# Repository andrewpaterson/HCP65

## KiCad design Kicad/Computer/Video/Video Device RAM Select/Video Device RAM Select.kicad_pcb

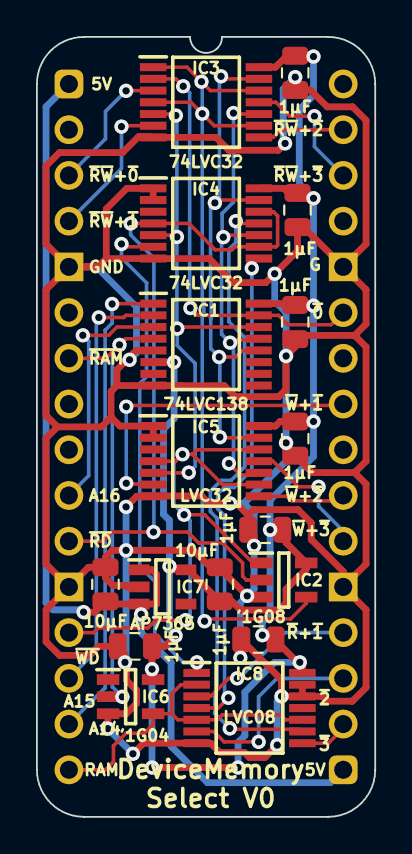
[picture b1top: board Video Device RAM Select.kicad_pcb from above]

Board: 2 copper layers, 18.8 x 43.3 mm, 18 parts (0 on the bottom side), 28 nets.

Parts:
C1, C2, C3, C4, C5, C6, C7: 1μF; C_0805
C8, C9: 10µF; C_0805
IC1: 74LVC138APW-Q100J; SOP65P640X110-16N
IC2: 74LVC1G08GV,125; SOT95P275X110-5N
IC3, IC4, IC5: 74LVC32APW,118; SOP65P640X110-14N
IC6: 74LVC1G04GV,125; SOT95P275X110-5N
IC7: AP7365-33WG-7; SOT95P285X130-5N
IC8: 74LVC08APW,112; SOP65P640X110-14N
J1: Board 2x16 W15.24mm; DIP-32_Board_W15.24mm

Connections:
5V: C8.1, IC7.1 (6VIn), IC7.3 (EN), J1.1, J1.17
(~RD·~WD)+~Device RAM 0: IC3.3 (1Y), J1.3
(~RD·~WD)+~Device RAM 1: IC3.6 (2Y), J1.4
(~RD·~WD)+~Device RAM 2: IC3.8 (3Y), J1.31
(~RD·~WD)+~Device RAM 3: IC3.11 (4Y), J1.30
/3.3V: C1.1, C2.1, C3.1, C4.1, C5.1, C6.1, C7.1, C9.1, IC1.6 (E3), IC1.16 (3V), IC2.5 (3V), IC3.14 (3V), IC4.14 (3V), IC5.14 (3V), IC6.5 (3V), IC7.5 (3.3VOut), IC8.14 (3V)
/~Device RAM 1: IC1.14 (~Y1), IC3.5 (2B), IC4.5 (2B), IC5.5 (2B)
/~Device RAM 2: IC1.13 (~Y2), IC3.10 (3B), IC4.10 (3B), IC5.10 (3B)
/~Device RAM 3: IC1.12 (~Y3), IC3.13 (4B), IC4.13 (4B), IC5.13 (4B)
/~RD+~Device RAM 1: IC4.6 (2Y), IC8.1 (1A)
/~RD+~Device RAM 2: IC4.8 (3Y), IC8.4 (2A)
/~RD+~Device RAM 3: IC4.11 (4Y), IC8.9 (3A)
/~RD·~WD: IC2.4 (Y), IC3.1 (1A), IC3.4 (2A), IC3.9 (3A), IC3.12 (4A)
A14: IC1.1 (A0), J1.15
A15: IC1.2 (A1), J1.14
A16: IC1.3 (A2), J1.10
Device RAM: IC6.4 (Y), IC8.2 (1B), IC8.5 (2B), IC8.10 (3B), J1.16
GND: C1.2, C2.2, C3.2, C4.2, C5.2, C6.2, C7.2, C8.2, C9.2, IC1.5 (~E2), IC1.8 (GND), IC2.3 (GND), IC3.7 (GND), IC4.1 (1A), IC4.2 (1B), IC4.7 (GND), IC5.1 (1A), IC5.2 (1B), IC5.7 (GND), IC6.3 (GND), IC7.2 (GND), IC8.7 (GND), IC8.12 (4A), IC8.13 (4B), J1.5, J1.12, J1.21, J1.28
~Device RAM 0: IC1.15 (~Y0), IC3.2 (1B), J1.27
~Device RAM: IC1.4 (~E1), IC6.2 (A), J1.7
~RD: IC2.2 (A), IC4.4 (2A), IC4.9 (3A), IC4.12 (4A), J1.11
~Read Device RAM 1: IC8.3 (1Y), J1.20
~Read Device RAM 2: IC8.6 (2Y), J1.19
~Read Device RAM 3: IC8.8 (3Y), J1.18
~WD: IC2.1 (B), IC5.4 (2A), IC5.9 (3A), IC5.12 (4A), J1.13
~WD+~Device RAM 1: IC5.6 (2Y), J1.25
~WD+~Device RAM 2: IC5.8 (3Y), J1.23
~WD+~Device RAM 3: IC5.11 (4Y), J1.22

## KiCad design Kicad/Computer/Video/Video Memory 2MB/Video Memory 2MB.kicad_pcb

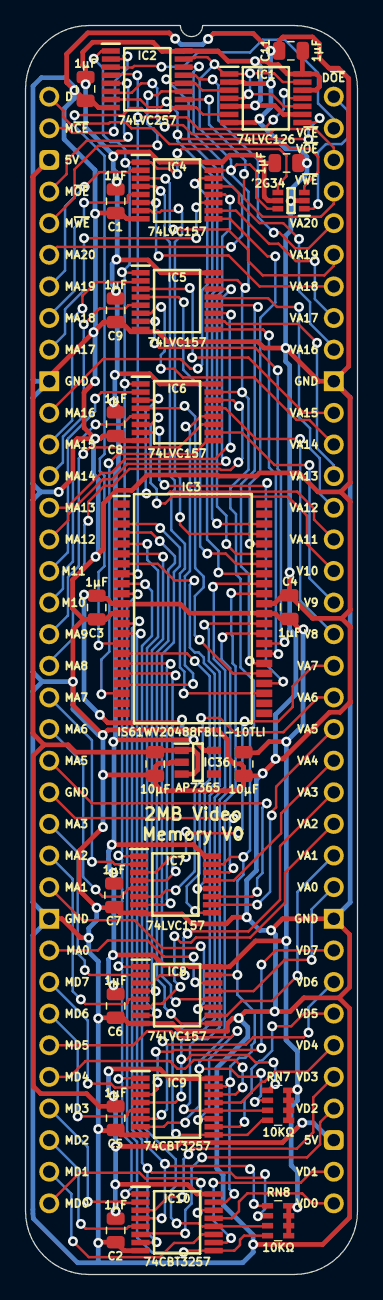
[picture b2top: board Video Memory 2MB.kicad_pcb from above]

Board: 2 copper layers, 26.7 x 100.3 mm, 29 parts (0 on the bottom side), 103 nets.

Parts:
C1, C2, C3, C4, C5, C6, C7, C8, C9, C10, C11, C12: 1μF; C_0805
C41, C42: 10μF; C_0805
IC1: 74LVC126APW-Q100J; SOP65P640X110-14N
IC2: 74LVC257APW,118; SOP65P640X110-16N
IC3: IS61WV20488FBLL-10TLI; SOP80P1176X120-44N
IC4, IC5, IC6, IC7, IC8: 74LVC157APW,118; SOP65P640X110-16N
IC9, IC10: SN74CBT3257CPWR; SOP65P640X120-16N
IC11: 74LVC2G34GW,125; 74LVC2G34GW125
IC36: AP7365-33WG-7; SOT95P285X130-5N
J3: Board 2x36 W22.86mm; DIP-72_Board_W22.86mm
RN7, RN8: CAY16-103J4LF; CAY16-J4

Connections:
5V: C2.1, C5.1, C41.1, IC9.16 (5V), IC10.16 (5V), IC36.1 (6VIn), IC36.3 (EN), J3.3, J3.39
/3.3V: C1.1, C3.1, C4.1, C6.1, C7.1, C8.1, C9.1, C10.1, C11.1, C12.1, C42.1, IC1.5 (2A), IC1.9 (3A), IC1.12 (4A), IC1.14 (3V), IC2.16 (3V), IC3.11 (3V), IC3.33 (3V), IC4.16 (3V), IC5.16 (3V), IC6.16 (3V), IC7.16 (3V), IC8.16 (3V), IC11.5 (3V), IC36.5 (3.3VOut), RN7.5 (R4), RN7.6 (R3), RN7.7 (R2), RN7.8 (R1), RN8.5 (R4), RN8.6 (R3), RN8.7 (R2), RN8.8 (R1)
/D: IC2.1 (S), IC4.1 (S), IC5.1 (S), IC6.1 (S), IC7.1 (S), IC8.1 (S), IC9.1 (S), IC10.1 (S), IC11.4 (2Y)
/D~OE: IC1.1 (1OE), IC1.4 (2OE), IC1.10 (3OE), IC1.13 (4OE), IC2.15 (~OE), IC4.15 (~E), IC5.15 (~E), IC6.15 (~E), IC7.15 (~E), IC8.15 (~E), IC9.15 (~OE), IC10.15 (~OE), IC11.6 (1Y)
/SA0: IC3.3 (A0), IC8.12 (4Y)
/SA1: IC3.4 (A1), IC8.9 (3Y)
/SA2: IC3.5 (A2), IC8.7 (2Y)
/SA3: IC3.6 (A3), IC8.4 (1Y)
/SA4: IC3.7 (A4), IC7.12 (4Y)
/SA5: IC3.16 (A5), IC7.9 (3Y)
/SA6: IC3.17 (A6), IC7.7 (2Y)
/SA7: IC3.18 (A7), IC7.4 (1Y)
/SA8: IC3.19 (A8), IC6.12 (4Y)
/SA9: IC3.20 (A9), IC6.9 (3Y)
/SA10: IC3.26 (A10), IC6.7 (2Y)
/SA11: IC3.27 (A11), IC6.4 (1Y)
/SA12: IC3.28 (A12), IC5.12 (4Y)
/SA13: IC3.29 (A13), IC5.9 (3Y)
/SA14: IC3.30 (A14), IC5.7 (2Y)
/SA15: IC3.38 (A15), IC5.4 (1Y)
/SA16: IC3.39 (A16), IC4.12 (4Y)
/SA17: IC3.40 (A17), IC4.9 (3Y)
/SA18: IC3.41 (A18), IC4.7 (2Y)
/SA19: IC3.25 (A19), IC4.4 (1Y)
/SA20: IC1.3 (1Y), IC2.12 (4Y), IC3.42 (A20)
/SD0: IC3.9 (D0), IC10.12 (4A), RN8.3 (R3)
/SD1: IC3.10 (D1), IC10.9 (3A), RN8.4 (R4)
/SD2: IC3.13 (D2), IC10.7 (2A), RN8.2 (R2)
/SD3: IC3.14 (D3), IC10.4 (1A), RN8.1 (R1)
/SD4: IC3.31 (D4), IC9.12 (4A), RN7.3 (R3)
/SD5: IC3.32 (D5), IC9.9 (3A), RN7.4 (R4)
/SD6: IC3.35 (D6), IC9.7 (2A), RN7.2 (R2)
/SD7: IC3.36 (D7), IC9.4 (1A), RN7.1 (R1)
/S~CE: IC1.11 (4Y), IC2.4 (1Y), IC3.8 (~CE)
/S~OE: IC1.8 (3Y), IC2.7 (2Y), IC3.37 (~OE)
/S~WE: IC1.6 (2Y), IC2.9 (3Y), IC3.15 (~WE)
D_{I}: IC11.3 (2A), J3.1
D~OE_{I}: IC11.1 (1A), J3.72
GND: C1.2, C2.2, C3.2, C4.2, C5.2, C6.2, C7.2, C8.2, C9.2, C10.2, C11.2, C12.2, C41.2, C42.2, IC1.2 (1A), IC1.7 (GND), IC2.8 (GND), IC3.12 (GND), IC3.34 (GND), IC4.8 (GND), IC5.8 (GND), IC6.8 (GND), IC7.8 (GND), IC8.8 (GND), IC9.8 (GND), IC10.8 (GND), IC11.2 (GND), IC36.2 (GND), J3.10, J3.27, J3.46, J3.63
MA0: IC8.14 (4I0), J3.28
MA1: IC8.11 (3I0), J3.26
MA2: IC8.5 (2I0), J3.25
MA3: IC8.2 (1I0), J3.24
MA4: IC7.14 (4I0), J3.23
MA5: IC7.11 (3I0), J3.22
MA6: IC7.5 (2I0), J3.21
MA7: IC7.2 (1I0), J3.20
MA8: IC6.14 (4I0), J3.19
MA9: IC6.11 (3I0), J3.18
MA10: IC6.5 (2I0), J3.17
MA11: IC6.2 (1I0), J3.16
MA12: IC5.14 (4I0), J3.15
MA13: IC5.11 (3I0), J3.14
MA14: IC5.5 (2I0), J3.13
MA15: IC5.2 (1I0), J3.12
MA16: IC4.14 (4I0), J3.11
MA17: IC4.11 (3I0), J3.9
MA18: IC4.5 (2I0), J3.8
MA19: IC4.2 (1I0), J3.7
MA20: IC2.14 (4I0), J3.6
MD0: IC10.14 (4B1), J3.36
MD1: IC10.11 (3B1), J3.35
MD2: IC10.5 (2B1), J3.34
MD3: IC10.2 (1B1), J3.33
MD4: IC9.14 (4B1), J3.32
MD5: IC9.11 (3B1), J3.31
MD6: IC9.5 (2B1), J3.30
MD7: IC9.2 (1B1), J3.29
M~CE: IC2.2 (1I0), J3.2
M~OE: IC2.5 (2I0), J3.4
M~WE: IC2.11 (3I0), J3.5
VA0: IC8.13 (4I1), J3.47
VA1: IC8.10 (3I1), J3.48
VA2: IC8.6 (2I1), J3.49
VA3: IC8.3 (1I1), J3.50
VA4: IC7.13 (4I1), J3.51
VA5: IC7.10 (3I1), J3.52
VA6: IC7.6 (2I1), J3.53
VA7: IC7.3 (1I1), J3.54
VA8: IC6.13 (4I1), J3.55
VA9: IC6.10 (3I1), J3.56
VA10: IC6.6 (2I1), J3.57
VA11: IC6.3 (1I1), J3.58
VA12: IC5.13 (4I1), J3.59
VA13: IC5.10 (3I1), J3.60
VA14: IC5.6 (2I1), J3.61
VA15: IC5.3 (1I1), J3.62
VA16: IC4.13 (4I1), J3.64
VA17: IC4.10 (3I1), J3.65
VA18: IC4.6 (2I1), J3.66
VA19: IC4.3 (1I1), J3.67
VA20: IC2.13 (4I1), J3.68
VD0: IC10.13 (4B2), J3.37
VD1: IC10.10 (3B2), J3.38
VD2: IC10.6 (2B2), J3.40
VD3: IC10.3 (1B2), J3.41
VD4: IC9.13 (4B2), J3.42
VD5: IC9.10 (3B2), J3.43
VD6: IC9.6 (2B2), J3.44
VD7: IC9.3 (1B2), J3.45
V~CE: IC2.3 (1I1), J3.71
V~OE: IC2.6 (2I1), J3.70
V~WE: IC2.10 (3I1), J3.69

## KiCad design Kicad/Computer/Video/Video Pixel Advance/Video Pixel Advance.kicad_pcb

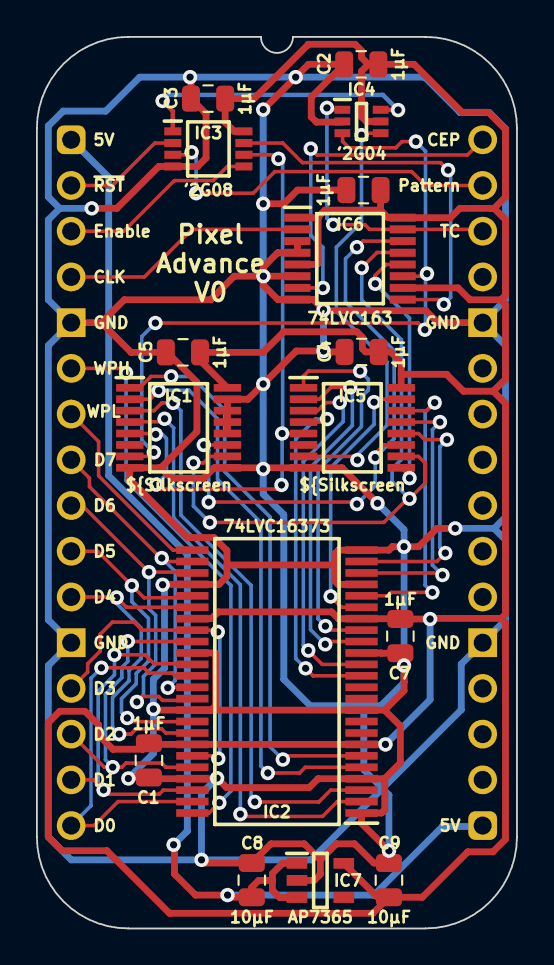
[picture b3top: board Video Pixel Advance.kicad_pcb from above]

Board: 2 copper layers, 26.7 x 49.5 mm, 17 parts (0 on the bottom side), 39 nets.

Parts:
C1, C2, C3, C4, C5, C6, C7: 1μF; C_0805
C8, C9: 10µF; C_0805
IC1, IC5: PI3B3251QE; SOP64P599X175-16N
IC2: 74LVC16373ADL,118; SOP64P1025X280-48N
IC3: 74LVC2G08DP-Q100H; SOP65P400X110-8N
IC4: 74LVC2G04GW-Q100H; SOP65P210X110-6N
IC6: 74LVC163PW,118; SOP65P640X110-16N
IC7: AP7365-33WG-7; SOT95P285X130-5N
J1: Board 2x16 W22.86mm; DIP-32_Board_W22.86mm

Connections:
5V: C8.1, IC7.1 (6VIn), IC7.3 (EN), J1.1, J1.17
/3.3V: C1.1, C2.1, C3.1, C4.1, C5.1, C6.1, C7.1, C9.1, IC1.16 (3V), IC2.7 (3V), IC2.18 (3V), IC2.31 (3V), IC2.42 (3V), IC3.8 (3V), IC4.5 (3V), IC5.16 (3V), IC6.1 (~MR), IC6.5 (D2), IC6.10 (CET), IC6.16 (3V), IC7.5 (3.3VOut)
/Q0: IC1.11 (S0), IC5.11 (S0), IC6.14 (Q0)
/Q1: IC1.10 (S1), IC5.10 (S1), IC6.13 (Q1)
/Q2: IC5.9 (S2), IC6.12 (Q2)
/Q3: IC1.7 (~OE), IC4.3 (2A), IC6.11 (Q3)
/RPS0: IC2.23 (2Q7), IC5.12 (I7)
/RPS1: IC2.22 (2Q6), IC5.13 (I6)
/RPS2: IC2.20 (2Q5), IC5.14 (I5)
/RPS3: IC2.19 (2Q4), IC5.15 (I4)
/RPS4: IC2.17 (2Q3), IC5.1 (I3)
/RPS5: IC2.16 (2Q2), IC5.2 (I2)
/RPS6: IC2.14 (2Q1), IC5.3 (I1)
/RPS7: IC2.13 (2Q0), IC5.4 (I0)
/RPS8: IC1.1 (I3), IC2.6 (1Q3)
/RPS9: IC1.2 (I2), IC2.5 (1Q2)
/RPS10: IC1.3 (I1), IC2.3 (1Q1)
/RPS11: IC1.4 (I0), IC2.2 (1Q0)
/Y: IC1.5 (Y), IC3.6 (2B), IC5.5 (Y)
/~PE: IC3.7 (1Y), IC6.9 (~PE)
/~Q3: IC4.4 (2Y), IC5.7 (~OE)
/~TC: IC3.1 (1A), IC4.6 (1Y)
CEP: IC6.7 (CEP), J1.32
CLK: IC6.2 (CP), J1.4
D0: IC2.36 (2D0), IC2.47 (1D0), J1.16
D1: IC2.35 (2D1), IC2.46 (1D1), J1.15
D2: IC2.33 (2D2), IC2.44 (1D2), J1.14
D3: IC2.32 (2D3), IC2.43 (1D3), J1.13
D4: IC2.30 (2D4), IC2.41 (1D4), J1.11
D5: IC2.29 (2D5), IC2.40 (1D5), J1.10
D6: IC2.27 (2D6), IC2.38 (1D6), J1.9
D7: IC2.26 (2D7), IC2.37 (1D7), J1.8
Enable Pattern: IC3.5 (2A), J1.3
GND: C1.2, C2.2, C3.2, C4.2, C5.2, C6.2, C7.2, C8.2, C9.2, IC1.8 (GND), IC1.9 (S2), IC1.12 (I7), IC1.13 (I6), IC1.14 (I5), IC1.15 (I4), IC2.1 (1~OE), IC2.4 (GND), IC2.10 (GND), IC2.15 (GND), IC2.21 (GND), IC2.24 (2~OE), IC2.28 (GND), IC2.34 (GND), IC2.39 (GND), IC2.45 (GND), IC3.4 (GND), IC4.2 (GND), IC5.8 (GND), IC6.3 (D0), IC6.4 (D1), IC6.6 (D3), IC6.8 (GND), IC7.2 (GND), J1.5, J1.12, J1.21, J1.28
Selected Pattern: IC3.3 (2Y), J1.31
TC: IC4.1 (1A), IC6.15 (TC), J1.30
Write Pattern High: IC2.25 (2LE), J1.7
Write Pattern Low: IC2.48 (1LE), J1.6
~Reset: IC3.2 (1B), J1.2

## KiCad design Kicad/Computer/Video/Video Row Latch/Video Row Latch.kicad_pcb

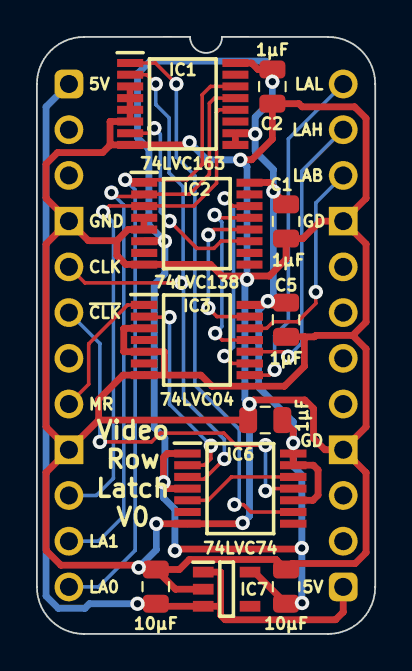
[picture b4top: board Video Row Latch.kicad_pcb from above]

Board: 2 copper layers, 18.8 x 33.2 mm, 12 parts (0 on the bottom side), 19 nets.

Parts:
C1, C2, C4, C5: 1μF; C_0805
C8, C9: 10μF; C_0805
IC1: 74LVC163PW,118; SOP65P640X110-16N
IC2: 74LVC138APW-Q100J; SOP65P640X110-16N
IC3: 74LVC04APW,118; SOP65P640X110-14N
IC6: 74LVC74APW,118; SOP65P640X110-14N
IC7: AP7365-33WG-7; SOT95P285X130-5N
J1: Board 2x12 W15.24mm; DIP-24_Board_W15.24mm

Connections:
5V: C8.1, IC7.1 (6VIn), IC7.3 (EN), J1.1, J1.13
/3.3V: C1.1, C2.1, C4.1, C5.1, C9.1, IC1.9 (~PE), IC1.10 (CET), IC1.16 (3V), IC2.6 (E3), IC2.16 (3V), IC3.14 (3V), IC6.1 (~1RD), IC6.4 (~1SD), IC6.10 (~2SD), IC6.13 (~2RD), IC6.14 (3V), IC7.5 (3.3VOut)
/CEP: IC1.7 (CEP), IC2.11 (~Y4)
/~Load Address Bank: IC2.12 (~Y3), IC3.13 (6A)
/~Load Address High: IC2.13 (~Y2), IC3.11 (5A)
/~Load Address Low: IC2.14 (~Y1), IC3.9 (4A)
/~MR: IC3.2 (1Y), IC6.2 (1D)
/~MR1: IC6.5 (1Q), IC6.12 (2D)
/~MR2: IC1.1 (~MR), IC6.9 (2Q)
CLK: IC1.2 (CP), IC6.3 (1CP), J1.5
GND: C1.2, C2.2, C4.2, C5.2, C8.2, C9.2, IC1.3 (D0), IC1.4 (D1), IC1.5 (D2), IC1.6 (D3), IC1.8 (GND), IC2.4 (~E1), IC2.5 (~E2), IC2.8 (GND), IC3.3 (2A), IC3.5 (3A), IC3.7 (GND), IC6.7 (GND), IC7.2 (GND), J1.4, J1.9, J1.16, J1.21
LA0: IC1.14 (Q0), IC2.1 (A0), J1.12
LA1: IC1.13 (Q1), IC2.2 (A1), J1.11
LA2: IC1.12 (Q2), IC2.3 (A2), J1.10
Load Address Bank: IC3.12 (6Y), J1.22
Load Address High: IC3.10 (5Y), J1.23
Load Address Low: IC3.8 (4Y), J1.24
MR: IC3.1 (1A), J1.8
~CLK: IC6.11 (2CP), J1.6

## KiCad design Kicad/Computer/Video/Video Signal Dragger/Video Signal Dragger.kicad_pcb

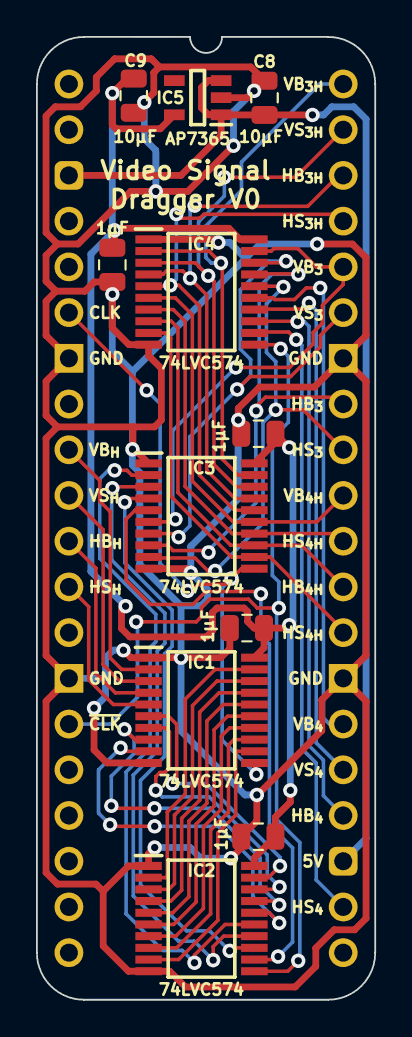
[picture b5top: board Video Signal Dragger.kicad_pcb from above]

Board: 2 copper layers, 18.8 x 53.5 mm, 12 parts (0 on the bottom side), 41 nets.

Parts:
C1, C2, C3, C4: 1μF; C_0805
C8, C9: 10µF; C_0805
IC1, IC2, IC3, IC4: 74LVC574APW,118; SOP65P640X110-20N
IC5: AP7365-33WG-7; SOT95P285X130-5N
J2: Board 2x20 W15.24mm; DIP-40_Board_W15.24mm

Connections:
5V: C8.1, IC5.1 (6VIn), IC5.3 (EN), J2.3, J2.23
/3.3V: C1.1, C2.1, C3.1, C4.1, C9.1, IC1.20 (3V), IC2.20 (3V), IC3.20 (3V), IC4.20 (3V), IC5.5 (3.3VOut)
/Horizontal Blank _{CYCLE 1H}: IC1.17 (Q2), IC2.4 (D2)
/Horizontal Blank _{CYCLE 1}: IC1.8 (D6), IC2.17 (Q2)
/Horizontal Blank _{CYCLE 2H}: IC1.13 (Q6), IC2.8 (D6)
/Horizontal Blank _{CYCLE 2}: IC2.13 (Q6), IC3.4 (D2)
/Horizontal Sync _{CYCLE 1H}: IC1.16 (Q3), IC2.5 (D3)
/Horizontal Sync _{CYCLE 1}: IC1.9 (D7), IC2.16 (Q3)
/Horizontal Sync _{CYCLE 2H}: IC1.12 (Q7), IC2.9 (D7)
/Horizontal Sync _{CYCLE 2}: IC2.12 (Q7), IC3.5 (D3)
/Vertical Blank _{CYCLE 1H}: IC1.19 (Q0), IC2.2 (D0)
/Vertical Blank _{CYCLE 1}: IC1.6 (D4), IC2.19 (Q0)
/Vertical Blank _{CYCLE 2H}: IC1.15 (Q4), IC2.6 (D4)
/Vertical Blank _{CYCLE 2}: IC2.15 (Q4), IC3.2 (D0)
/Vertical Sync _{CYCLE 1H}: IC1.18 (Q1), IC2.3 (D1)
/Vertical Sync _{CYCLE 1}: IC1.7 (D5), IC2.18 (Q1)
/Vertical Sync _{CYCLE 2H}: IC1.14 (Q5), IC2.7 (D5)
/Vertical Sync _{CYCLE 2}: IC2.14 (Q5), IC3.3 (D1)
GND: C1.2, C2.2, C3.2, C4.2, C8.2, C9.2, IC1.1 (~OE), IC1.10 (GND), IC2.1 (~OE), IC2.10 (GND), IC3.1 (~OE), IC3.10 (GND), IC4.1 (~OE), IC4.10 (GND), IC5.2 (GND), J2.7, J2.14, J2.27, J2.34
Horizontal Blank _{CYCLE 3H}: IC3.17 (Q2), IC4.4 (D2), J2.38
Horizontal Blank _{CYCLE 3}: IC3.8 (D6), IC4.17 (Q2), J2.33
Horizontal Blank _{CYCLE 4H}: IC3.13 (Q6), IC4.8 (D6), J2.29
Horizontal Blank _{CYCLE 4}: IC4.13 (Q6), J2.24
Horizontal Blank _{HALF CYCLE}: IC1.4 (D2), J2.11
Horizontal Sync _{CYCLE 3H}: IC3.16 (Q3), IC4.5 (D3), J2.37
Horizontal Sync _{CYCLE 3}: IC3.9 (D7), IC4.16 (Q3), J2.32
Horizontal Sync _{CYCLE 4H}: IC3.12 (Q7), IC4.9 (D7), J2.28
Horizontal Sync _{CYCLE 4}: IC4.12 (Q7), J2.22
Horizontal Sync _{HALF CYCLE}: IC1.5 (D3), J2.12
Pixel CLK: IC1.11 (CP), IC3.11 (CP), J2.6
Vertical Blank _{CYCLE 3H}: IC3.19 (Q0), IC4.2 (D0), J2.40
Vertical Blank _{CYCLE 3}: IC3.6 (D4), IC4.19 (Q0), J2.36
Vertical Blank _{CYCLE 4H}: IC3.15 (Q4), IC4.6 (D4), J2.31
Vertical Blank _{CYCLE 4}: IC4.15 (Q4), J2.26
Vertical Blank _{HALF CYCLE}: IC1.2 (D0), J2.9
Vertical Sync _{CYCLE 3H}: IC3.18 (Q1), IC4.3 (D1), J2.39
Vertical Sync _{CYCLE 3}: IC3.7 (D5), IC4.18 (Q1), J2.35
Vertical Sync _{CYCLE 4H}: IC3.14 (Q5), IC4.7 (D5), J2.30
Vertical Sync _{CYCLE 4}: IC4.14 (Q5), J2.25
Vertical Sync _{HALF CYCLE}: IC1.3 (D1), J2.10
~Pixel CLK: IC2.11 (CP), IC4.11 (CP), J2.15

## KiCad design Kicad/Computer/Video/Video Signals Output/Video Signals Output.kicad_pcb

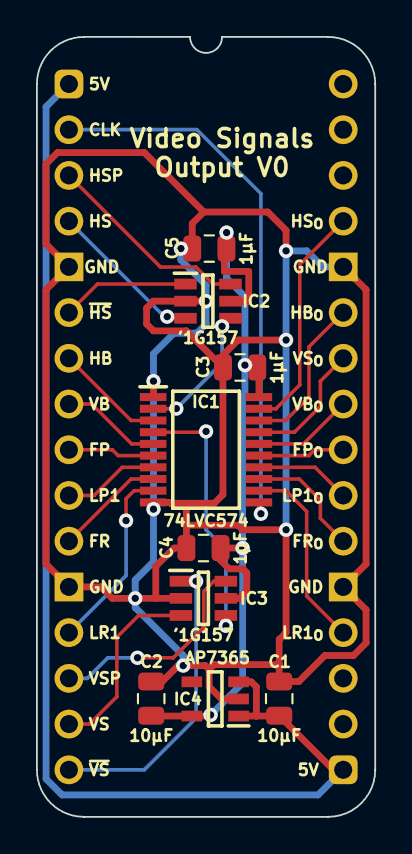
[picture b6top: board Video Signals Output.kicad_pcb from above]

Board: 2 copper layers, 18.8 x 43.3 mm, 10 parts (0 on the bottom side), 26 nets.

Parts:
C1, C2: 10µF; C_0805
C3, C4, C5: 1μF; C_0805
IC1: 74LVC574APW,118; SOP65P640X110-20N
IC2, IC3: 74LVC1G157GV,125; 74LVC1G157GV125
IC4: AP7365-33WG-7; SOT95P285X130-5N
J1: Board 2x16 W15.24mm; DIP-32_Board_W15.24mm

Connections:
5V: C1.1, IC4.1 (6VIn), IC4.3 (EN), J1.1, J1.17
/3.3V: C2.1, C3.1, C4.1, C5.1, IC1.20 (3V), IC2.5 (3V), IC3.5 (3V), IC4.5 (3.3VOut)
/Horizontal Sync _{SEL}: IC1.2 (D0), IC2.4 (Y)
/Vertical Sync _{SEL}: IC1.4 (D2), IC3.4 (Y)
CLK: IC1.11 (CP), J1.2
First Pixel: IC1.6 (D4), J1.9
First Pixel _{HALF CYCLE}: IC1.15 (Q4), J1.24
First Row: IC1.8 (D6), J1.11
First Row _{HALF CYCLE}: IC1.13 (Q6), J1.22
GND: C1.2, C2.2, C3.2, C4.2, C5.2, IC1.1 (~OE), IC1.10 (GND), IC2.2 (GND), IC3.2 (GND), IC4.2 (GND), J1.5, J1.12, J1.21, J1.28
Horizontal Blank: IC1.3 (D1), J1.7
Horizontal Blank _{HALF CYCLE}: IC1.18 (Q1), J1.27
Horizontal Sync: IC2.3 (I0), J1.4
Horizontal Sync Polarity: IC2.6 (S), J1.3
Horizontal Sync _{HALF CYCLE}: IC1.19 (Q0), J1.29
Last Pixel + 1: IC1.7 (D5), J1.10
Last Pixel + 1 _{HALF CYCLE}: IC1.14 (Q5), J1.23
Last Row + 1: IC1.9 (D7), J1.13
Last Row + 1 _{HALF CYCLE}: IC1.12 (Q7), J1.20
Vertical Blank: IC1.5 (D3), J1.8
Vertical Blank _{HALF CYCLE}: IC1.16 (Q3), J1.25
Vertical Sync: IC3.3 (I0), J1.15
Vertical Sync Polarity: IC3.6 (S), J1.14
Vertical Sync _{HALF CYCLE}: IC1.17 (Q2), J1.26
~Horizontal Sync: IC2.1 (I1), J1.6
~Vertical Sync: IC3.1 (I1), J1.16

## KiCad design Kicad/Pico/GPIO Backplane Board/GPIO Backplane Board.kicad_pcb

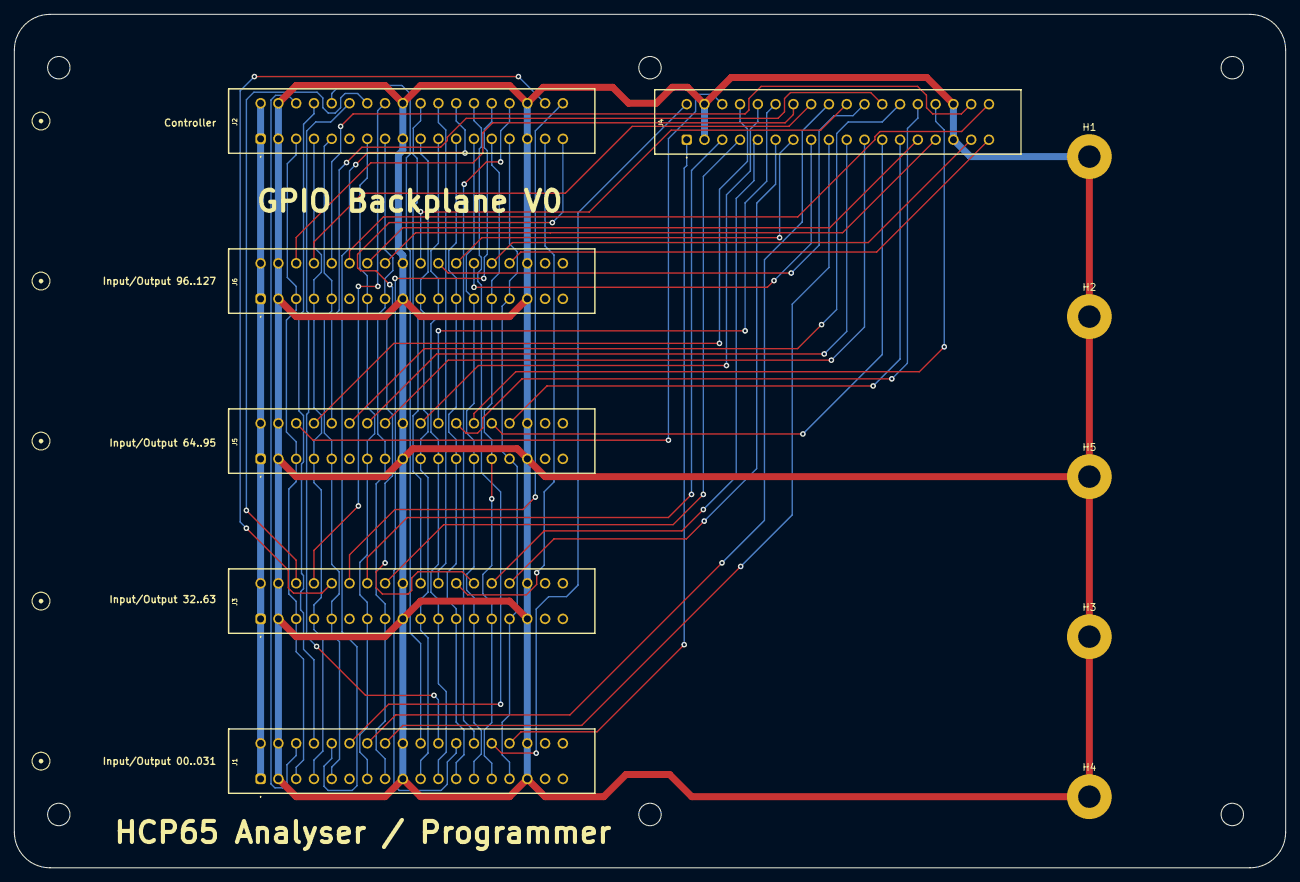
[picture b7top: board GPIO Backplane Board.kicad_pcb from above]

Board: 2 copper layers, 181.6 x 121.9 mm, 22 parts (0 on the bottom side), 61 nets.

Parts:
B1, B2, B3, B4: HCP65_GPIO_32bit_Board
B5: HCP65_GPIO_Controller_Board
H1, H2, H3, H4, H5: MountingHole_Pad; MountingHole_3.2mm_M3_Pad
H6, H7, H8, H9, H10, H11: MountingHole; MountingHole_3.2mm_M3
J1, J2, J3, J4, J5, J6: 2-5530843-7; 255308437

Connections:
/12V: J1.1, J1.2, J2.1, J2.2, J3.1, J3.2, J5.1, J5.2, J6.1, J6.2
/D0: J1.13, J2.13, J3.13, J5.13, J6.13
/D1: J1.15, J2.15, J3.15, J5.15, J6.15
/D2: J1.19, J2.19, J3.19, J5.19, J6.19
/D3: J1.21, J2.21, J3.21, J5.21, J6.21
/D4: J1.23, J2.23, J3.23, J5.23, J6.23
/D5: J1.25, J2.25, J3.25, J5.25, J6.25
/D6: J1.27, J2.27, J3.27, J5.27, J6.27
/D7: J1.29, J2.29, J3.29, J5.29, J6.29
/GND: H1.1, H2.1, H3.1, H4.1, H5.1, J1.3, J1.4, J1.17, J1.18, J1.31, J1.32, J2.3, J2.4, J2.17, J2.18, J2.31, J2.32, J3.3, J3.4, J3.17, J3.18, J3.31, J3.32, J4.3, J4.4, J4.31, J4.32, J5.3, J5.4, J5.17, J5.18, J5.31, J5.32, J6.3, J6.4, J6.17, J6.18, J6.31, J6.32
/Read GD B0 _{0..7}: J1.6, J2.6
/Read GD B0 _{8..15}: J1.8, J2.8
/Read GD B0 _{16..23}: J1.20, J2.10
/Read GD B0 _{24..31}: J1.22, J2.12
/Read GD B0 _{32..39}: J2.14, J3.6
/Read GD B0 _{40..47}: J2.16, J3.8
/Read GD B0 _{48..55}: J2.20, J3.20
/Read GD B0 _{56..63}: J2.22, J3.22
/Read GD B1 _{0..7}: J4.6, J5.6
/Read GD B1 _{8..15}: J4.8, J5.8
/Read GD B1 _{16..23}: J4.10, J5.20
/Read GD B1 _{24..31}: J4.12, J5.22
/Read GD B1 _{32..39}: J4.14, J6.6
/Read GD B1 _{40..47}: J4.16, J6.8
/Read GD B1 _{48..55}: J4.20, J6.20
/Read GD B1 _{56..63}: J4.22, J6.22
/Read GPIO _{ALL}: J1.7, J2.7, J3.7, J5.7, J6.7
/Write Enable: J1.5, J2.5, J3.5, J5.5, J6.5
/Write GD B0 _{0..7}: J1.10, J2.24
/Write GD B0 _{8..15}: J1.12, J2.26
/Write GD B0 _{16..23}: J1.24, J2.28
/Write GD B0 _{24..31}: J1.26, J2.30
/Write GD B0 _{32..39}: J2.34, J3.10
/Write GD B0 _{40..47}: J2.36, J3.12
/Write GD B0 _{48..55}: J2.33, J3.24
/Write GD B0 _{56..63}: J2.35, J3.26
/Write GD B1 _{0..7}: J4.24, J5.10
/Write GD B1 _{8..15}: J4.26, J5.12
/Write GD B1 _{16..23}: J4.28, J5.24
/Write GD B1 _{24..31}: J4.30, J5.26
/Write GD B1 _{32..39}: J4.34, J6.10
/Write GD B1 _{40..47}: J4.36, J6.12
/Write GD B1 _{48..55}: J4.13, J6.24
/Write GD B1 _{56..63}: J4.15, J6.26
/Write GPIO _{ALL}: J1.9, J2.9, J3.9, J5.9, J6.9
/Write OE B0 _{0..7}: J1.14, J4.18
/Write OE B0 _{8..15}: J1.16, J4.17
/Write OE B0 _{16..23}: J1.28, J4.2
/Write OE B0 _{24..31}: J1.30, J4.1
/Write OE B0 _{32..39}: J3.14, J4.5
/Write OE B0 _{40..47}: J3.16, J4.7
/Write OE B0 _{48..55}: J3.28, J4.9
/Write OE B0 _{56..63}: J3.30, J4.11
/Write OE B1 _{0..7}: J4.19, J5.14
/Write OE B1 _{8..15}: J4.21, J5.16
/Write OE B1 _{16..23}: J4.23, J5.28
/Write OE B1 _{24..31}: J4.25, J5.30
/Write OE B1 _{32..39}: J4.27, J6.14
/Write OE B1 _{40..47}: J4.29, J6.16
/Write OE B1 _{48..55}: J4.33, J6.28
/Write OE B1 _{56..63}: J4.35, J6.30

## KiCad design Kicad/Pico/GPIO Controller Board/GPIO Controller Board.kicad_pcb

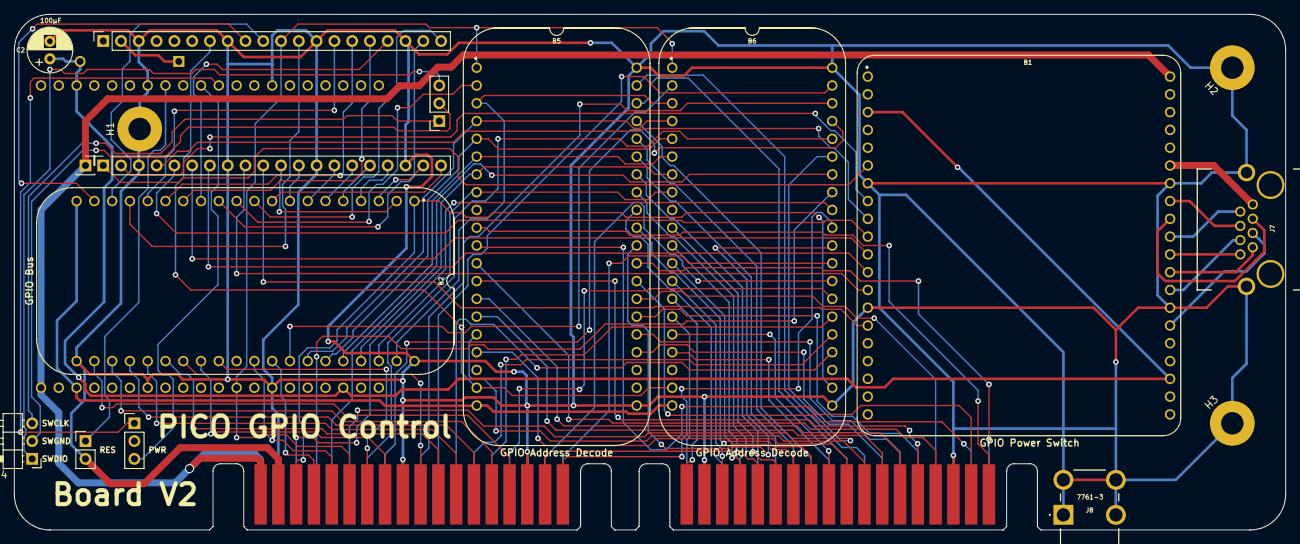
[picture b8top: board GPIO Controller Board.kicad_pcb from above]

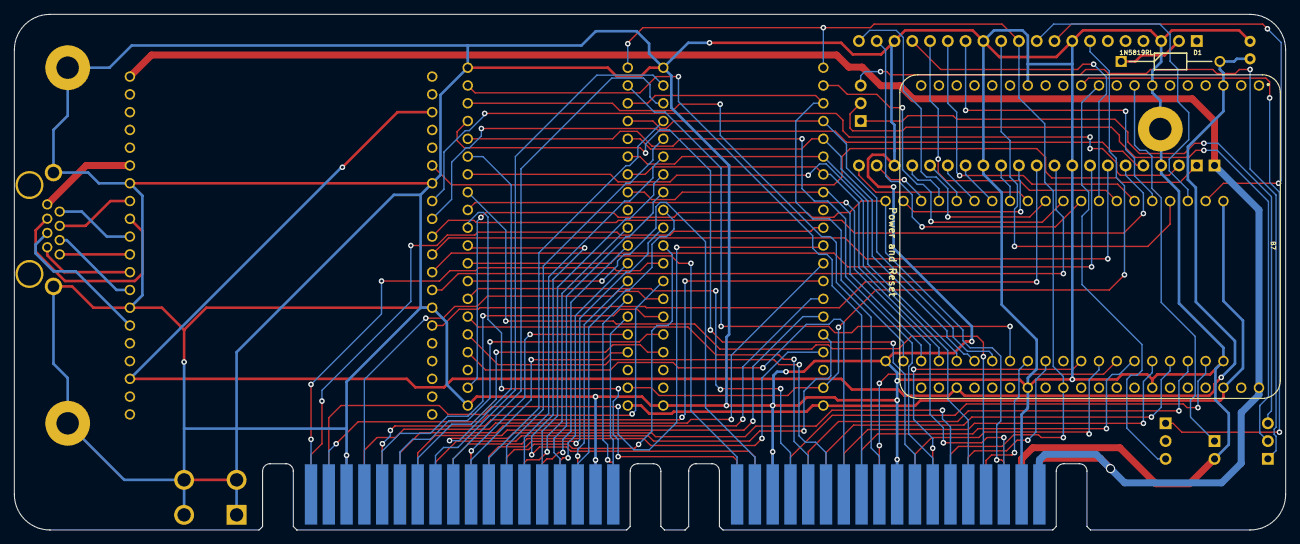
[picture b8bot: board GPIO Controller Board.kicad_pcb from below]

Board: 2 copper layers, 181.6 x 73.7 mm, 21 parts (2 on the bottom side), 113 nets.

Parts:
B1: GPIO Power Switch; HCP65_GPIO_Power_Switch
B2: GPIO Bus; HCP65_GPIO_Bus
B5, B6: Pico GPIO Address Decode; HCP65_GPIO_Address_Decode
B7: Power and Reset; HCP65_Power_and_Reset
C2: 100μF; CP_Radial_D6.3mm_P2.50mm
D1: 1N5819RL; DIOAD1414W86L464D238
H1, H2, H3: MountingHole_Pad; MountingHole_3.2mm_M3_Pad
J1: Conn_01x03_Pin; PinSocket_1x03_P2.54mm_Vertical
J2, J3: 2-5530843-7; 36pin Edge Connector
J4: Conn_01x03_Pin; PinHeader_1x03_P2.54mm_Horizontal
J5, J6: Conn_01x20_Pin; PinSocket_1x20_P2.54mm_Vertical
J7: 1-406541-1; 1-406541-1_1
J8: 7761-3; 77613
J9: Conn_01x03_Pin; PinHeader_1x03_P2.54mm_Vertical
J10: Conn_01x02_Pin; PinHeader_1x02_P2.54mm_Vertical
J11: Conn_01x01_Pin; PinSocket_1x01_P2.54mm_Vertical

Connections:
/3.3V: B2.20 (3.3V), B5.20 (3.3V), B6.20 (3.3V), B7.38 (3.3V)
/5V: B1.3 (5V), B1.23 (5V), B7.3 (5V), B7.23 (5V), C2.1, D1.2
/5V_{A} EN: B1.8 (5Va_{EN}), J5.2
/5V_{B} EN: B1.9 (5Vb_{EN}), J5.4
/5V_{C} EN: B1.10 (5Vc_{EN}), J5.5
/5V_{OUT1}: B1.33 (5Vc_{OUT}), J7.4
/5V_{OUT2}: B1.32 (5Vb_{OUT}), J7.3
/5V_{OUT3}: B1.31 (5Va_{OUT}), J7.2
/12V: B1.40 (12V), B7.40 (12V), J2.1, J2.2, J11.1
/12V EN: B1.6 (12V_{EN}), J5.1
/12V_{OUT}: B1.35 (12_{OUT}), J7.1
/18V: B7.10 (18V), J9.3
/A0: B2.8 (A0), J5.12
/A1: B2.7 (A1), J5.14
/A2: B2.6 (A2), J5.15
/A3: B2.5 (A3), J5.16
/A4: B2.4 (A4), J5.17
/A5: B2.3 (A5), J5.19
/AA0: B2.38 (AA0), B5.8 (A0), B6.8 (A0)
/AA1: B2.37 (AA1), B5.7 (A1), B6.7 (A1)
/AA2: B2.36 (AA2), B5.6 (A2), B6.6 (A2)
/AA3: B2.35 (AA3), B5.5 (A3), B6.5 (A3)
/AA4: B2.34 (AA4), B5.4 (A4), B6.4 (A4)
/AA5: B2.33 (AA5), B6.2 (~A_{Enable2})
/AA_{Enable}: B2.39 (AA_Enable), B5.3 (A_{Enable}1), B6.3 (A_{Enable}1)
/A_{Enable}: B2.2 (A_Enable), J5.11
/D0: B2.12 (D0), J6.19
/D1: B2.13 (D1), J6.17
/D2: B2.14 (D2), J6.16
/D3: B2.15 (D3), J6.15
/D4: B2.16 (D4), J6.14
/D5: B2.17 (D5), J6.12
/D6: B2.18 (D6), J6.10
/D7: B2.19 (D7), J6.9
/DD0: B2.29 (DD0), J2.13
/DD1: B2.28 (DD1), J2.15
/DD2: B2.27 (DD2), J2.19
/DD3: B2.26 (DD3), J2.21
/DD4: B2.25 (DD4), J2.23
/DD5: B2.24 (DD5), J2.25
/DD6: B2.23 (DD6), J2.27
/DD7: B2.22 (DD7), J2.29
/Enable GPIO: B5.19 (Enable), B6.19 (Enable), J6.7
/GND: B1.7 (GND), B1.14 (GND), B1.27 (GND), B1.34 (GND), B2.21 (GND), B2.40 (GND), B5.21 (GND), B5.40 (GND), B6.21 (GND), B6.40 (GND), B7.7 (GND), B7.14 (GND), B7.27 (GND), B7.34 (GND), C2.2, H1.1, H2.1, H3.1, J2.3, J2.4, J2.17, J2.18, J2.31, J2.32, J3.3, J3.4, J3.31, J3.32, J5.3, J5.8, J5.13, J5.18, J6.3, J6.8, J6.13, J6.18, J7.MH1, J7.MH2, J8.1, J8.2, J8.3, J8.4, J10.2
/GND_{A} EN: B1.11 (GNDa_{EN}), J5.6
/GND_{B} EN: B1.12 (GNDb_{EN}), J5.7
/GND_{C} EN: B1.13 (GNDc_{EN}), J5.9
/GND_{D} EN: B1.15 (GNDd_{EN}), J5.10
/GND_{OUT1}: B1.30 (GNDd_{OUT}), J7.8
/GND_{OUT2}: B1.29 (GNDc_{OUT}), J7.7
/GND_{OUT3}: B1.28 (GNDb_{OUT}), J7.6
/GND_{OUT4}: B1.26 (GNDa_{OUT}), J7.5
/PWR_{SW}: B7.11 (PWR_{SW}), J9.1
/RES_{SW}: B7.8 (RES_{SW}), J10.1
/RRead GPIO _{ALL}: B2.32 (RRead_GPIO), J2.7
/Read GD B0 _{0..7}: B6.32 (Read_GD__{0..7}), J2.6
/Read GD B0 _{8..15}: B6.33 (Read_GD__{8..15}), J2.8
/Read GD B0 _{16..23}: B6.34 (Read_GD__{16..23}), J2.10
/Read GD B0 _{24..31}: B6.35 (Read_GD__{24..31}), J2.12
/Read GD B0 _{32..39}: B6.36 (Read_GD__{32..39}), J2.14
/Read GD B0 _{40..47}: B6.37 (Read_GD__{40..47}), J2.16
/Read GD B0 _{48..55}: B6.38 (Read_GD__{48..55}), J2.20
/Read GD B0 _{56..63}: B6.39 (Read_GD__{56..63}), J2.22
/Read GD B1 _{0..7}: B5.32 (Read_GD__{0..7}), J3.6
/Read GD B1 _{8..15}: B5.33 (Read_GD__{8..15}), J3.8
/Read GD B1 _{16..23}: B5.34 (Read_GD__{16..23}), J3.10
/Read GD B1 _{24..31}: B5.35 (Read_GD__{24..31}), J3.12
/Read GD B1 _{32..39}: B5.36 (Read_GD__{32..39}), J3.14
/Read GD B1 _{40..47}: B5.37 (Read_GD__{40..47}), J3.16
/Read GD B1 _{48..55}: B5.38 (Read_GD__{48..55}), J3.20
/Read GD B1 _{56..63}: B5.39 (Read_GD__{56..63}), J3.22
/Read GPIO _{ALL}: B2.9 (Read_GPIO), J5.20
/SWCLK: J1.1, J4.3
/SWDIO: J1.3, J4.1
/SWGND: J1.2, J4.2
/WWrite GPIO _{ALL}: B2.31 (WWrite_GPIO), J2.9
/Write Enable: B2.1 (Write_Enable), B6.22 (Write_Enable), J2.5
/Write GD B0 _{0..7}: B6.24 (Write_GD__{0..7}), J2.24
/Write GD B0 _{8..15}: B6.25 (Write_GD__{8..15}), J2.26
/Write GD B0 _{16..23}: B6.26 (Write_GD__{16..23}), J2.28
/Write GD B0 _{24..31}: B6.27 (Write_GD__{24..31}), J2.30
/Write GD B0 _{32..39}: B6.28 (Write_GD__{32..39}), J2.34
/Write GD B0 _{40..47}: B6.29 (Write_GD__{40..47}), J2.36
/Write GD B0 _{48..55}: B6.30 (Write_GD__{48..55}), J2.33
/Write GD B0 _{56..63}: B6.31 (Write_GD__{56..63}), J2.35
/Write GD B1 _{0..7}: B5.24 (Write_GD__{0..7}), J3.24
/Write GD B1 _{8..15}: B5.25 (Write_GD__{8..15}), J3.26
/Write GD B1 _{16..23}: B5.26 (Write_GD__{16..23}), J3.28
/Write GD B1 _{24..31}: B5.27 (Write_GD__{24..31}), J3.30
/Write GD B1 _{32..39}: B5.28 (Write_GD__{32..39}), J3.34
/Write GD B1 _{40..47}: B5.29 (Write_GD__{40..47}), J3.36
/Write GD B1 _{48..55}: B5.30 (Write_GD__{48..55}), J3.13
/Write GD B1 _{56..63}: B5.31 (Write_GD__{56..63}), J3.15
/Write GPIO _{ALL}: B2.10 (Write_GPIO), J6.20
/Write OE B0 _{0..7}: B6.17 (Write_OE__{0..7}), J3.18
/Write OE B0 _{8..15}: B6.16 (Write_OE__{8..15}), J3.17
/Write OE B0 _{16..23}: B6.15 (Write_OE__{16..23}), J3.2
/Write OE B0 _{24..31}: B6.14 (Write_OE__{24..31}), J3.1
/Write OE B0 _{32..39}: B6.13 (Write_OE__{32..39}), J3.5
/Write OE B0 _{40..47}: B6.12 (Write_OE__{40..47}), J3.7
/Write OE B0 _{48..55}: B6.11 (Write_OE__{48..55}), J3.9
/Write OE B0 _{56..63}: B6.10 (Write_OE__{56..63}), J3.11
/Write OE B1 _{0..7}: B5.17 (Write_OE__{0..7}), J3.19
/Write OE B1 _{8..15}: B5.16 (Write_OE__{8..15}), J3.21
/Write OE B1 _{16..23}: B5.15 (Write_OE__{16..23}), J3.23
/Write OE B1 _{24..31}: B5.14 (Write_OE__{24..31}), J3.25
/Write OE B1 _{32..39}: B5.13 (Write_OE__{32..39}), J3.27
/Write OE B1 _{40..47}: B5.12 (Write_OE__{40..47}), J3.29
/Write OE B1 _{48..55}: B5.11 (Write_OE__{48..55}), J3.33
/Write OE B1 _{56..63}: B5.10 (Write_OE__{56..63}), J3.35
/~A5: B2.11 (~A5), B5.2 (~A_{Enable2})
/~Reset: B5.1 (~Reset), B6.1 (~Reset), B7.29 (~RES_{3V}), J2.11, J6.11
unnamed: D1.1, J6.2
